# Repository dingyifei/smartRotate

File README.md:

# smartRotate
 A display rotation software with hardware integration

## Folders

and why they exist

### ```F401```

it is the firmware for my dev board written in C/C++ STM32CUBE. It allows the device to communicate with the computer using USBHID to report it's position.

### ```python```

A python implementation of a software with GUI to automatically or manually adjust the orientation of the monitor.

### ```Hardware```

KiCad and other stuff for the hardware to be functional 

### ```Linux```

Linux driver for communicating with the board

### ```Windows```

Windows driver for communicating with the board

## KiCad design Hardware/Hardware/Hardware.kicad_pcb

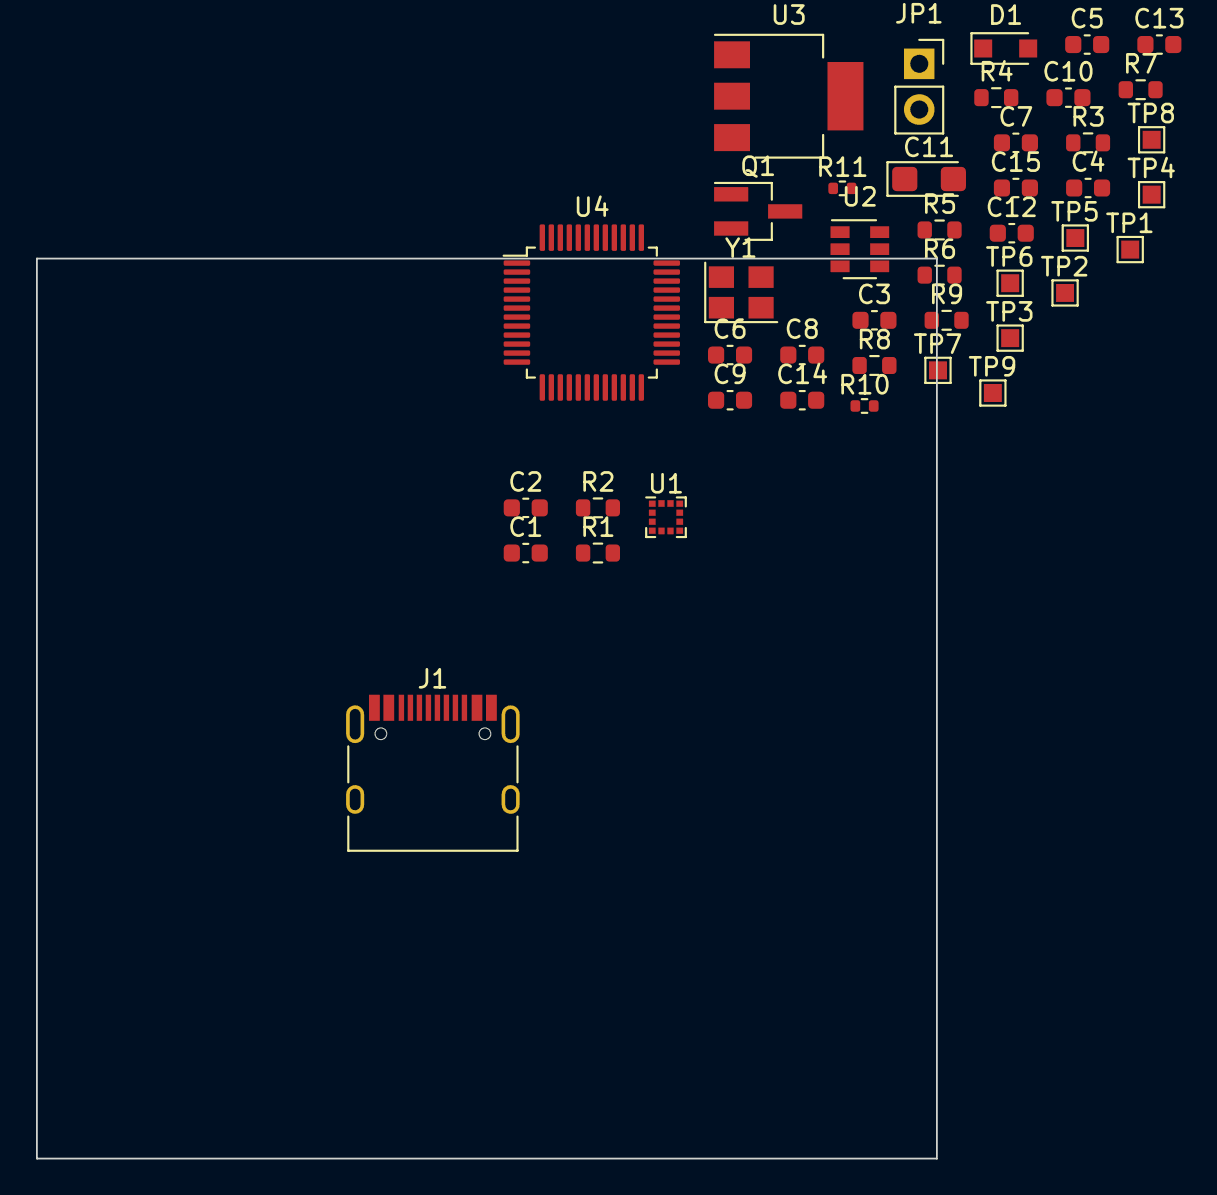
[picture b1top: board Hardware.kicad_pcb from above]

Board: 4 copper layers, 50.0 x 50.0 mm, 44 parts (0 on the bottom side), 18 nets, no tracks yet.

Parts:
C1, C2, C7, C9, C10, C12: 100nF; C_0603_1608Metric
C3, C4: 10pF; C_0603_1608Metric
C5: 100nf; C_0603_1608Metric
C6, C8: 10uf; C_0603_1608Metric
C11: 22uf/10v; CP_EIA-3216-18_Kemet-A
C13: 4.7uf; C_0603_1608Metric
C14: 10nF; C_0603_1608Metric
C15: 1uf; C_0603_1608Metric
D1: 1N4148WS; D_SOD-323_HandSoldering
J1: TYPE-C-31-M-12; USB_C_Receptacle_HRO_TYPE-C-31-M-12
JP1: Jumper_NO_Small; PinSocket_1x02_P2.54mm_Vertical
Q1: MMUN2112LT1G; SOT-23_Handsoldering
R1, R2, R3, R9: 1.5k; R_0603_1608Metric
R4: 47k; R_0603_1608Metric
R5: 4.7k; R_0603_1608Metric
R6: 100k; R_0603_1608Metric
R7, R8: 56k; R_0603_1608Metric
R10, R11: 22; R_0402_1005Metric
TP1, TP2, TP3, TP4, TP5, TP6, TP7, TP8, TP9: TestPoint; TestPoint_Pad_1.0x1.0mm
U1: BMA253; LGA-12_2x2mm_P0.5mm
U2: USBLC6-2SC6; SOT-23-6
U3: AZ1117CH-3.3TRG1; SOT-223-3_TabPin2
U4: STM32F303CCT6; LQFP-48_7x7mm_P0.5mm
Y1: 8Mhz 10pf; Crystal_SMD_3225-4Pin_3.2x2.5mm

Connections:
+3V3: C1.1, C2.1, C7.1, C9.1, C10.1, C11.1, C12.1, C13.1, C14.1, C15.1, JP1.2, R1.1, R2.1, R9.2, TP6.1, U1.3, U1.7, U1.11, U3.2, U4.1, U4.9, U4.24, U4.36, U4.48
+5V: C8.1, J1.A4, J1.A9, J1.B4, J1.B9, R7.2, R8.2, TP7.1, U2.5, U3.3
/MCU/BOOT0: C6.2, D1.1, R6.1, TP5.1, U4.44
/MCU/CC1: J1.A5, R7.1
/MCU/CC2: J1.B5, R8.1
/MCU/D+: R10.2, U4.33
/MCU/D-: R11.2, U4.32
/MCU/NRST: C5.1, Q1.2, TP2.1, U4.7
/MCU/OSC_IN: C3.2, U4.5, Y1.1
/MCU/OSC_OUT: R3.1, U4.6
/MCU/USB_D+: J1.A6, J1.B6, R9.1, R10.1, TP1.1, U2.1, U2.6
/MCU/USB_D-: J1.A7, J1.B7, R11.1, TP4.1, U2.3, U2.4
/SCL: R1.2, TP9.1, U1.12, U4.38
/SDA: R2.2, TP3.1, U1.2, U4.37
GND: C1.2, C2.2, C3.1, C4.1, C5.2, C6.1, C7.2, C8.2, C9.2, C10.2, C11.2, C12.2, C13.2, C14.2, C15.2, J1.A1, J1.A12, J1.B1, J1.B12, J1.S1, Q1.3, R4.2, R6.2, TP8.1, U1.1, U1.4, U1.8, U1.9, U2.2, U3.1, U4.8, U4.23, U4.35, U4.47, Y1.2, Y1.4
unnamed: C4.2, R3.2, Y1.3
unnamed: D1.2, JP1.1, R5.1
unnamed: Q1.1, R4.1, R5.2

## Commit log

2020-04-12 Finally something is functional??
2020-04-13 SPI finally can print things!
2020-04-23 Things are coming together, maybe I can finish the important part in one/two weeks after ap exam?
2020-04-24 I think I fix most things and it would work
2020-04-25 rename some things, trying to figure out the _h and _l, write those tomorrow
2020-05-01 I don't know how to write C++....
2020-05-01 some useful info here
2020-05-03 I know it is a bad implementation, but at least it can show a menu to you
2020-05-08 start developing the hardware
2020-05-27 improvement
2020-05-27 Fix the bug when obtaining monitor settings, it can function now.
2020-05-28 add the primary option for the Accelerometer, some footprint change to put a real biased transistor
2020-05-28 update Schematic make everything looks nice
2020-06-01 fix some mistake on wiring, use ListBox instead of menubutton
2020-06-04 Writing driver for LSM303DLHC
2020-06-05 fix some problems, refactor
2020-06-05 It can RUN but the numbers it give have no use
2020-06-05 fix soem bug
2020-06-05 i guess i can't solve the problem today
2020-06-09 last update before I switch brach
2020-08-29 say goodbye to the L3GD220 and LSM303. They are obsolete parts no one cares about.
2020-08-31 rewrite in progress
2020-08-31 Monitors() should work now
2020-08-31 it should work now, at least partialy
2020-08-31 reformat and edd space for docstring
2020-08-31 small changes on Monitor
    allow monitor to be initialize with device and config parameter. prepare everything for the save config functions
2020-08-31 improve documentation and type hints
2020-09-01 add some tests
2020-09-01 I know my code is awful and this implementation is not beautiful
2020-09-01 modify gitignore, add function to save a "Monitor" object in json
2020-09-01 read json file to a monitor object
2020-09-01 make everything clean and nice
2020-09-01 OO programming lol
2020-09-01 Enough progress today
2020-09-02 Switch to QT5 so I can make a functional UI
2020-09-02 50% of the gui works now
2020-09-02 I know the bat doesn't work.
2020-09-04 tiny improvement
2020-09-04 Ready to port the board
2020-09-05 I mean it works now....
2020-09-05 im just genna keep .hg as is for now
2020-09-05 This lib is worse than I was expecting
2020-09-05 remove old MPU6050 lib, I can't fix it so I give up fixing it
2020-09-06 before I test something
2020-09-06 This is the fix I was searching for!
2020-09-06 it works now
2020-09-08 I mean it's kinda silly to spent 3 days to find out compiler setting somehow changed the readings into nonsense........................
2020-09-11 prep my code
2020-09-24 better doc, allow a profile to be saved
2020-09-26 Making progress by getting rid of mbed
2020-09-26 Update mpu6050
2020-09-28 .cpp allows class
2020-09-30 it kinda works?
2020-10-06 Bump electron from 9.0.2 to 10.1.3 in /Electron
    Bumps [electron](https://github.com/electron/electron) from 9.0.2 to 10.1.3.
    - [Release notes](https://github.com/electron/electron/releases)
    - [Changelog](https://github.com/electron/electron/blob/master/docs/breaking-changes.md)
    - [Commits](https://github.com/electron/electron/compare/v9.0.2...v10.1.3)
2020-10-07 "introduce new bugs"
2020-10-07 code cleanup
2020-10-07 update GPIO
2020-10-07 Oviously it doesn't like my auto refactor
2020-10-07 Configure the 1 ms timer and code reformat config improvement
2020-10-07 temporary solution to having out of date HAL
2020-10-07 hmmmmmmm needs more work, add some files
2020-10-07 generate the magic interrupt
2020-10-07 Figure out USB later
2021-01-25 Change to 4 layer board
2021-07-28 I got an idea
2023-09-06 Bump electron from 10.1.3 to 22.3.21 in /Electron
    Bumps [electron](https://github.com/electron/electron) from 10.1.3 to 22.3.21.
    - [Release notes](https://github.com/electron/electron/releases)
    - [Changelog](https://github.com/electron/electron/blob/main/docs/breaking-changes.md)
    - [Commits](https://github.com/electron/electron/compare/v10.1.3...v22.3.21)
    ---
    updated-dependencies:
2023-10-05 Bump electron from 10.1.3 to 22.3.25 in /Electron
    Bumps [electron](https://github.com/electron/electron) from 10.1.3 to 22.3.25.
    - [Release notes](https://github.com/electron/electron/releases)
    - [Changelog](https://github.com/electron/electron/blob/main/docs/breaking-changes.md)
    - [Commits](https://github.com/electron/electron/compare/v10.1.3...v22.3.25)
    ---
    updated-dependencies:
